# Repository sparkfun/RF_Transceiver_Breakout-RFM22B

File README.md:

SparkFun RF Transceiver Breakout - RFM22B-S2 (434 MHz)
=======================================================

[*SparkFun RF Transceiver Breakout - RFM22B-S2 (434 MHz) (WRL-10154)*](https://www.sparkfun.com/products/10154)

Here is the breakout board for the RFM22B which gives you access to the pins. 
The RFM22B is a low-cost ISM (industrial, scientific, and medical) FSK (frequency-shift keying) transceiver module which offers communication at 434MHz and adjustable output power of up to +17 dBm. 
The wide operating voltage range of 1.8–3.6 V and low current consumption makes the RFM22 an ideal solution for battery powered applications.

Repository Contents
-------------------

* **/Firmware** - Example code 
* **/Hardware** - Eagle design files (.brd, .sch)
* **/Production** - Production panel files (.brd)

Documentation
--------------
* **[SparkFun Fritzing repo](https://github.com/sparkfun/Fritzing_Parts)** - Fritzing diagrams for SparkFun products.
* **[SparkFun 3D Model repo](https://github.com/sparkfun/3D_Models)** - 3D models of SparkFun products. 

License Information
-------------------
This product is _**open source**_! 

The **hardware** is released under [Creative Commons ShareAlike 4.0 International](https://creativecommons.org/licenses/by-sa/4.0/).

The **code** is beerware; if you see me (or any other SparkFun employee) at the local, and you've found our code helpful, please buy us a round!

Please use, reuse, and modify these files as you see fit. Please maintain attribution to SparkFun Electronics and release anything derivative under the same license.

Distributed as-is; no warranty is given.

- Your friends at SparkFun.

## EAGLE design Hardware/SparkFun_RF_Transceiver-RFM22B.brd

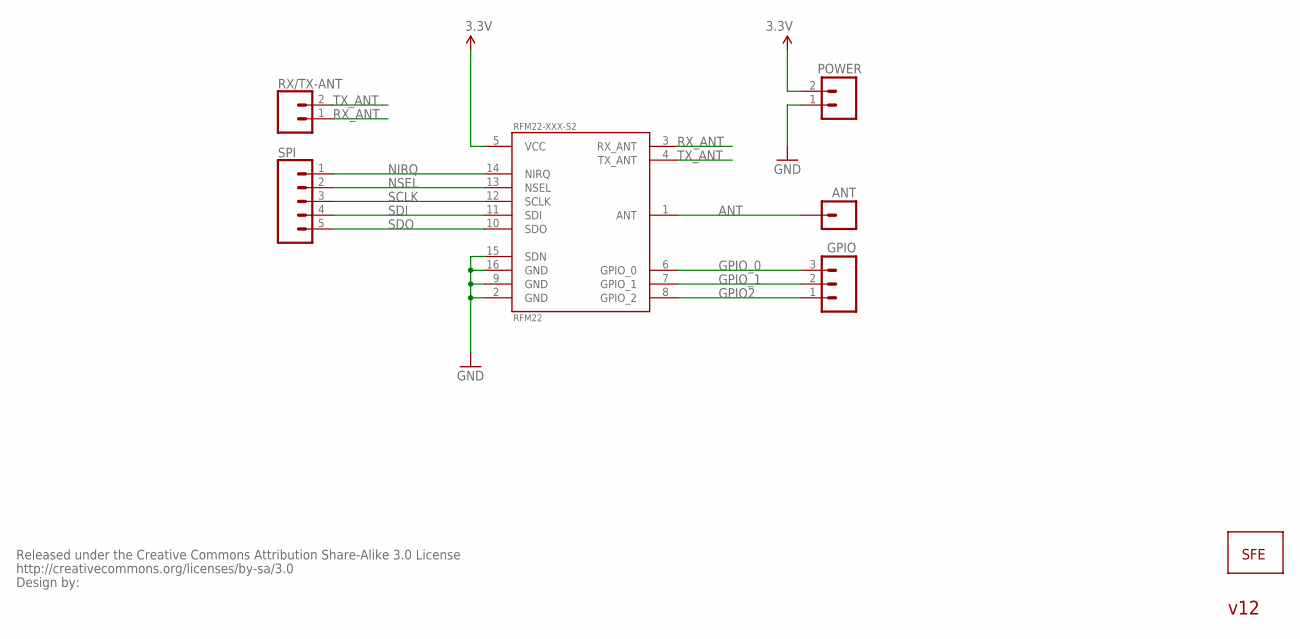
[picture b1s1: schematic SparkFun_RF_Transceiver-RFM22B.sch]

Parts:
JP0: POWER; 1X02
JP1: LOGO-SFENEW; SFE-NEW-WEBLOGO
JP2: ANT; 1X01
JP3: GPIO; 1X03
JP4: SPI; 1X05
JP5: RX/TX-ANT; 1X02
RFM22-XXX-S2: RFM22; RFM22-XXX-S2
U$1: CREATIVE_COMMONS

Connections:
3.3V: JP0.2, RFM22-XXX-S2.5 (VCC)
ANT: JP2.1, RFM22-XXX-S2.1 (ANT)
GND: JP0.1, RFM22-XXX-S2.2 (GND), RFM22-XXX-S2.9 (GND), RFM22-XXX-S2.15 (SDN), RFM22-XXX-S2.16 (GND)
GPIO2: JP3.1, RFM22-XXX-S2.8 (GPIO_2)
GPIO_0: JP3.3, RFM22-XXX-S2.6 (GPIO_0)
GPIO_1: JP3.2, RFM22-XXX-S2.7 (GPIO_1)
NIRQ: JP4.1, RFM22-XXX-S2.14 (NIRQ)
NSEL: JP4.2, RFM22-XXX-S2.13 (NSEL)
RX_ANT: JP5.1, RFM22-XXX-S2.3 (RX_ANT)
SCLK: JP4.3, RFM22-XXX-S2.12 (SCLK)
SDI: JP4.4, RFM22-XXX-S2.11 (SDI)
SDO: JP4.5, RFM22-XXX-S2.10 (SDO)
TX_ANT: JP5.2, RFM22-XXX-S2.4 (TX_ANT)

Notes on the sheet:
v12

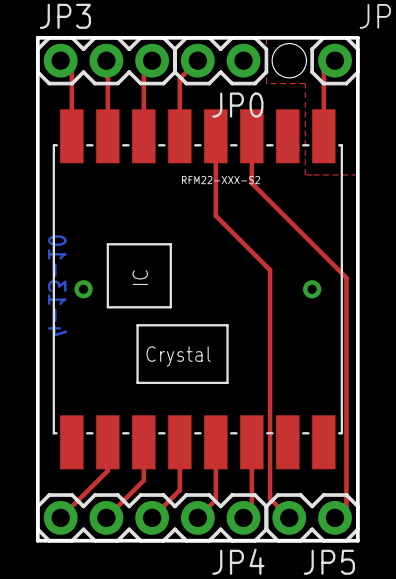
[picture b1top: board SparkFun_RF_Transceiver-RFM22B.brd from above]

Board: 2 copper layers, 17.8 x 27.9 mm, 8 parts (1 on the bottom side), 13 nets.

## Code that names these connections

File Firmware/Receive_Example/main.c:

/*
    Created on: Mar. 30, 2010
	Under project: RFM22
	Author: Jim Lindblom
	RFM22 Receive Example
	
	Hardware: Arduino Pro (ATmega328) running at 8Mhz, 3.3V
	Wiring:
	RFM22 BOB	|	Arduino Pro
	----------------------------
		GND		|	GND
		3.3V	|	3.3V
		GPIO0	|	NC
		GPIO1	|	NC
		GPIO2	|	NC
		RXANT	|	PD6 (D6)
		TXANT	|	PD5 (D5)
		IRQ		|	PD4 (D4)
		CSN		|	PB0 (D8)
		SCK		|	PB4 (D13)
		SDI		|	PB2 (D11)
		SDO		|	PB3 (D12)
		
	Antenna is a 17cm piece of wire sticking straight up into the air.
*/

//======================//
//======================//
#include <avr/io.h>
#include <stdio.h>
#include "RFM22.h"
//======================//
//======================//

#define sbi(var, mask)   ((var) |= (uint8_t)(1 << mask))
#define cbi(var, mask)   ((var) &= (uint8_t)~(1 << mask))

//======================//
//Arduino Pro Specific Defines
#define LED 5

//RFM22 Defines
#define CS 0 //pin for chip select
#define TXANT 5	// PD5
#define RXANT 6	// PD6
#define NIRQ 4	// PD4

//======================//
//======================//

void ioinit(void);
void delay_ms(uint16_t x);
void delay_us(uint16_t x);

//======================//
//======================//

static int uart_putchar(char c, FILE *stream);
uint8_t uart_getchar(void);
static FILE mystdout = FDEV_SETUP_STREAM(uart_putchar, NULL, _FDEV_SETUP_WRITE);

//======================//
//======================//

void init_SPI(void);
void init_RFM22(void);
void to_rx_mode(void);
void rx_reset(void);
void checkINT(void);
void txdata(char data);
char rxdata(void);
char read(uint8_t address);
void write(uint8_t address, char data);

//======================//
//Global Variables
unsigned char RF_RXBUF[35];

int main(void)
{
	unsigned char i, chksum;

	ioinit();
	init_SPI();
	sbi(PORTB,CS);
	printf("********RFM22 Communication Test********\n");

	//====================//
	//Communications Test
	printf("Reading DTYPE register, should be 0x08: %d", read(DTYPE));
	
	printf("\n*****************************************\n\n");
	
	init_RFM22();	// Initialize all RFM22 registers
	printf("Entering RX Mode...\n");
	to_rx_mode();
	
	while(1)
	{
		if((PIND & (1<<NIRQ)) == 0)	//Interrupt will be generated if data is recieved
		{
			// Read 18-byte packet into RF_RXBUF[]:
			for(i=0; i<17; i++)
			{
				RF_RXBUF[i] = read(0x7F);
			}
			
			// Check that the checksum matches up:
			chksum = 0;
			for(i=0; i<16; i++)
				chksum += RF_RXBUF[i];
		
			// If checksum is good, print out what was received into the terminal
			if(chksum == RF_RXBUF[16])
			{
				write(0x07, 0x01);	// To ready mode
				printf("Received: ");
				for(i=0; i<17; i++)
					printf("%c", RF_RXBUF[i]);	// Print characters if passed the checksum
				printf("\n");
				//printf("To Ready mode\n");
			}
			// otherwise reset and start listening again
			else
			{
				rx_reset();
				//printf("Bad checksum RX RESET...Listening again\n");
			}
			delay_ms(50);
		}
	}
}

// Initialize the RFM22 for transmitting
void init_RFM22(void)
{
	write(INTEN2, 0x00);	// Disable all interrupts
	write(OMFC1, 0x01);		// Set READY mode
	write(0x09, 0x7F);		// Cap = 12.5pF
	write(0x0A, 0x05);		// Clk output is 2MHz
	
	write(0x0B, 0xF4);		// GPIO0 is for RX data output
	write(0x0C, 0xEF);		// GPIO1 is TX/RX data CLK output
	write(0x0D, 0x00);		// GPIO2 for MCLK output
	write(0x0E, 0x00);		// GPIO port use default value
	
	write(0x0F, 0x70);		// NO ADC used
	write(0x10, 0x00);		// no ADC used
	write(0x12, 0x00);		// No temp sensor used
	write(0x13, 0x00);		// no temp sensor used
	
	write(0x70, 0x20);		// No manchester code, no data whiting, data rate < 30Kbps
	
	write(0x1C, 0x1D);		// IF filter bandwidth
	write(0x1D, 0x40);		// AFC Loop
	//write(0x1E, 0x0A);	// AFC timing
	
	write(0x20, 0xA1);		// clock recovery
	write(0x21, 0x20);		// clock recovery
	write(0x22, 0x4E);		// clock recovery
	write(0x23, 0xA5);		// clock recovery
	write(0x24, 0x00);		// clock recovery timing
	write(0x25, 0x0A);		// clock recovery timing
	
	//write(0x2A, 0x18);
	write(0x2C, 0x00);
	write(0x2D, 0x00);
	write(0x2E, 0x00);
	
	write(0x6E, 0x27);		// TX data rate 1
	write(0x6F, 0x52);		// TX data rate 0
	
	write(0x30, 0x8C);		// Data access control
	
	write(0x32, 0xFF);		// Header control
	
	write(0x33, 0x42);		// Header 3, 2, 1, 0 used for head length, fixed packet length, synchronize word length 3, 2,
	
	write(0x34, 64);		// 64 nibble = 32 byte preamble
	write(0x35, 0x20);		// 0x35 need to detect 20bit preamble
	write(0x36, 0x2D);		// synchronize word
	write(0x37, 0xD4);
	write(0x38, 0x00);
	write(0x39, 0x00);
	write(0x3A, 's');		// set tx header 3
	write(0x3B, 'o');		// set tx header 2
	write(0x3C, 'n');		// set tx header 1
	write(0x3D, 'g');		// set tx header 0
	write(0x3E, 17);		// set packet length to 17 bytes
	
	write(0x3F, 's');		// set rx header
	write(0x40, 'o');
	write(0x41, 'n');
	write(0x42, 'g');
	write(0x43, 0xFF);		// check all bits
	write(0x44, 0xFF);		// Check all bits
	write(0x45, 0xFF);		// check all bits
	write(0x46, 0xFF);		// Check all bits
	
	write(0x56, 0x01);
	
	write(0x6D, 0x07);		// Tx power to max
	
	write(0x79, 0x00);		// no frequency hopping
	write(0x7A, 0x00);		// no frequency hopping
	
	write(0x71, 0x22);		// GFSK, fd[8]=0, no invert for TX/RX data, FIFO mode, txclk-->gpio
	
	write(0x72, 0x48);		// Frequency deviation setting to 45K=72*625
	
	write(0x73, 0x00);		// No frequency offset
	write(0x74, 0x00);		// No frequency offset
	
	write(0x75, 0x53);		// frequency set to 434MHz
	write(0x76, 0x64);		// frequency set to 434MHz
	write(0x77, 0x00);		// frequency set to 434Mhz
	
	write(0x5A, 0x7F);
	write(0x59, 0x40);
	write(0x58, 0x80);
	
	write(0x6A, 0x0B);
	write(0x68, 0x04);
	write(0x1F, 0x03);
}

void to_rx_mode(void)
{
	write(0x07, 0x01);	// to ready mode
	
	sbi(PORTD, RXANT);
	cbi(PORTD, TXANT);
	delay_ms(50);
	rx_reset();
}

void rx_reset(void)
{
	unsigned char i;
	
	write(0x07, 0x01);	// to ready mode
	
	i = read(0x03);
	i = read(0x04);
	
	write(0x7E, 17);
	
	write(0x08, 0x03);
	write(0x08, 0x00);
	
	write(0x07, 5);
	
	write(0x05, 2);
}

void checkINT(void)
{
	if ((PIND & (1<<NIRQ)) == 0)
		printf("INT == 0\n");
	else
		printf("INT == 1\n");
}

void write(uint8_t address, char data)
{
	//write any data byte to any single address
	//adds a 0 to the MSB of the address byte (WRITE mode)
	
	address |= 0x80;

	cbi(PORTB,CS);
	delay_ms(1);
	txdata(address);
	delay_ms(1);
	txdata(data);
	delay_ms(1);
	sbi(PORTB,CS);
}

char read(uint8_t address)
{
	//returns the contents of any 1 byte register from any address
	//sets the MSB for every address byte (READ mode)

	char byte;

	address &= 0x7F;

	cbi(PORTB,CS);
	txdata(address);
	byte = rxdata();
	sbi(PORTB,CS);

	return byte;
}

char rxdata(void)
{
	SPDR = 0x55;
	while((SPSR&0x80) == 0x00);

	return SPDR;
}

void txdata(char data)
{
	SPDR = data;
	while((SPSR&0x80) == 0x00);
}

void init_SPI(void)
{
	// enable SPI
	// make SPI master
	// SCLK idle low
	// sample data on rising edge
	// SPCR |= 0b01010011;	// SPIclk = FOSC/128
	SPCR |= 0b01010000;	// SPIclk = Fosc/4
}

static int uart_putchar(char c, FILE *stream)
{
    if (c == '\n') uart_putchar('\r', stream);

    loop_until_bit_is_set(UCSR0A, UDRE0);
    UDR0 = c;

    return 0;
}

uint8_t uart_getchar(void)
{
    while( !(UCSR0A & (1<<RXC0)) );
    return(UDR0);
}


void ioinit (void)
{
    //1 = output, 0 = input
    DDRB = 0b11101111; //MISO input
    DDRC = 0b11111111; //All outputs
    DDRD = 0b11101110; //PORTD (RX on PD0), PD4 input
	stdout = &mystdout; //Required for printf init
	int MYUBRR = 103;
	UBRR0H = (MYUBRR) >> 8;
	UBRR0L = MYUBRR;
	UCSR0B = (1<<RXEN0)|(1<<TXEN0);
	UCSR0C = (3<<UCSZ00);
	UCSR0A = (1<<U2X0);

	TCCR2B = (1<<CS21);
	
	cbi(PORTD, TXANT);
	cbi(PORTD, RXANT);
}

//General short delays
void delay_ms(uint16_t x)
{
    for (; x > 0 ; x--)
        delay_us(1000);
}

//General short delays
void delay_us(uint16_t x)
{
    while(x > 256)
    {
        TIFR2 = (1<<TOV2); //Clear any interrupt flags on Timer2
        TCNT2 = 0; //256 - 125 = 131 : Preload timer 2 for x clicks. Should be 1us per click
        while( (TIFR2 & (1<<TOV2)) == 0);

        x -= 256;
    }

    TIFR2 = (1<<TOV2); //Clear any interrupt flags on Timer2
    TCNT2= 256 - x; //256 - 125 = 131 : Preload timer 2 for x clicks. Should be 1us per click
    while( (TIFR2 & (1<<TOV2)) == 0);
}

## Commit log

2015-05-07 Adding hardware, example code

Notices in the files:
parts and their libraries:
SparkFun: Released under the Creative Commons Attribution Share-Alike 3.0 License
SparkFun: http://creativecommons.org/licenses/by-sa/3.0
